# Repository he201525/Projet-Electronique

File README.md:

# Welcome in our Group Project for a course of Electricity!

***

We are a group of 4 students from EPHEC louvain la neuve. 
***

* Aymeric Ponjee
* Zita Almasy 
* Thibaut Hermant  
* Gauthier Bohyn

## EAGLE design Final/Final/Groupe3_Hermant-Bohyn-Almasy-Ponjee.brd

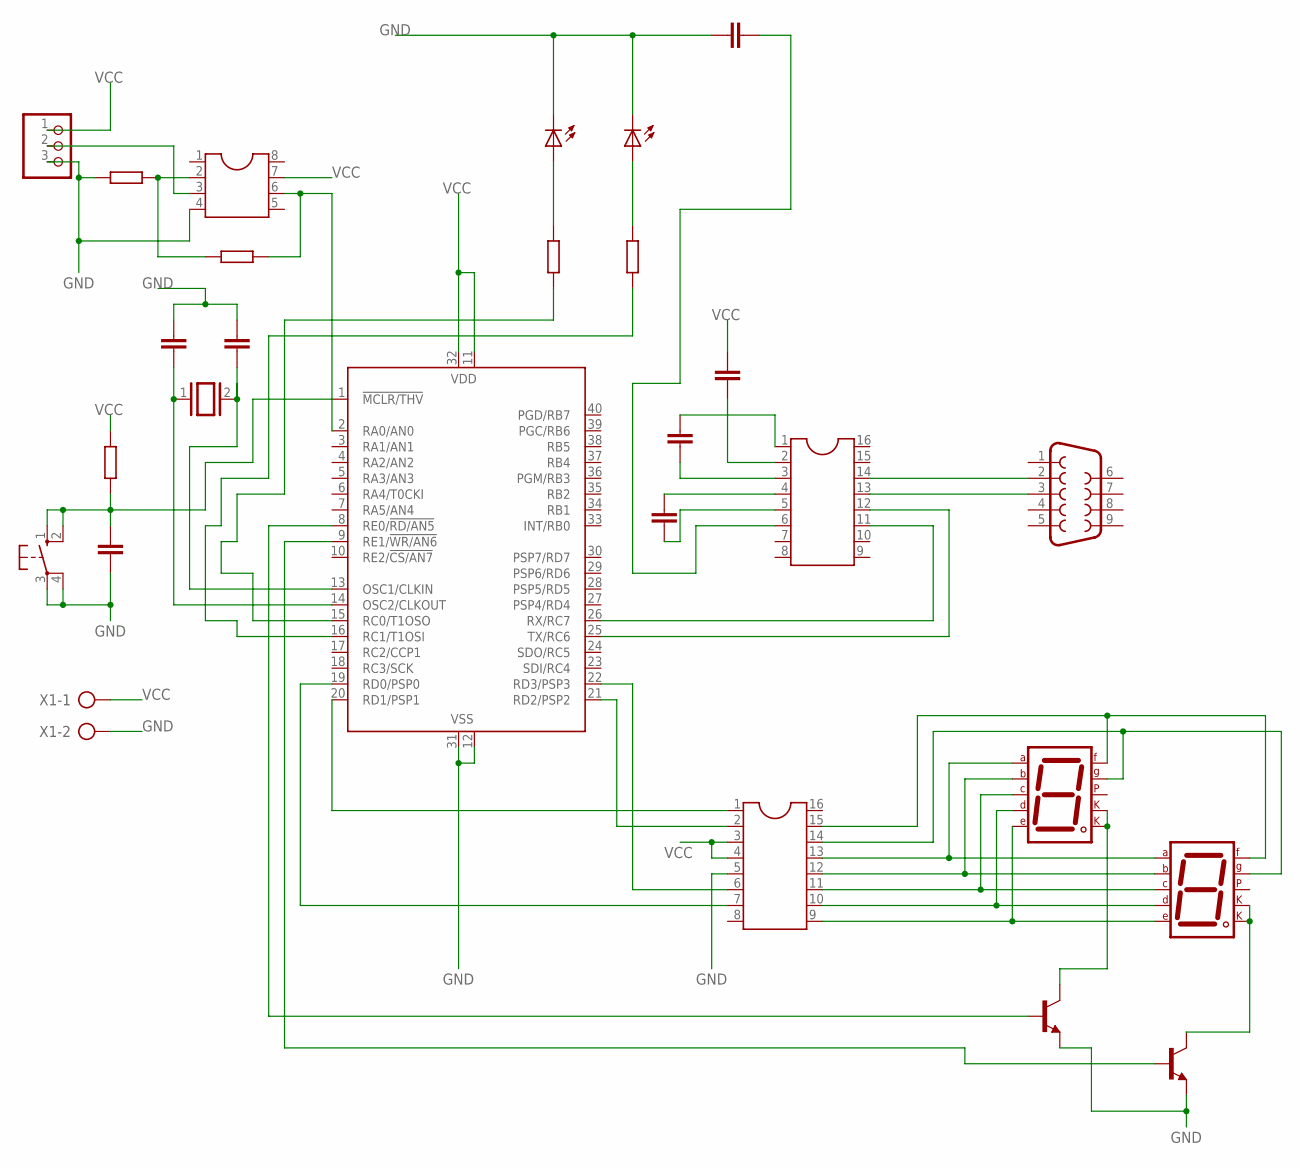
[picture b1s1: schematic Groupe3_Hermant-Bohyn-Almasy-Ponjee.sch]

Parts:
4511: DIL16
AMPLIOP: DIL8; DIL08
C1, C2: 15pF; C025-050X050
C3: 1uF; C025-050X050
C4, C5, C7, C61: 10uF; C025-050X050
D1, D2: 7SEG-CK; 7SEG-13
LED1, LED2: LED_ELD260; LED_LD260
LM35: PINHD-1X3; 1X03
MAX232: DIL16
P1/COMPIM: F09V
Q1, Q2: 2N2222; TO18
R1: 10k; 0204/7
R2: 4k; 0204/7
R3: 1k; 0204/7
R4, R5: 280; 0204/7
S1: 10-XX; B3F-10XX
U1: PIC16F877P; DIL40
X1: AK300/2
X11: XTAL/S; QS

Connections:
COMPIM: 4511.12, D1.6 (B), D2.6 (B)
GND: 4511.5, AMPLIOP.4, C1.1, C2.1, C3.1, C61.2, LED1.K (C), LED2.K (C), LM35.3, Q1.1 (E), Q2.1 (E), R2.1, S1.3, S1.4 (P1), U1.12 (VSS), U1.31 (VSS), X1.2
unnamed: C2.2, U1.14 (OSC2/CLKOUT), X11.1
unnamed: MAX232.14, P1/COMPIM.2
unnamed: LED2.A, R5.2
unnamed: C1.2, U1.13 (OSC1/CLKIN), X11.2
unnamed: 4511.1, U1.20 (RD1/PSP1)
unnamed: LED1.A, R4.2
unnamed: MAX232.13, P1/COMPIM.3
unnamed: C61.1, MAX232.6
unnamed: R4.1, U1.15 (RC0/T1OSO)
unnamed: R5.1, U1.16 (RC1/T1OSI)
unnamed: C7.1, MAX232.2
unnamed: C4.1, MAX232.3
unnamed: C4.2, MAX232.1
unnamed: C5.2, MAX232.4
unnamed: C5.1, MAX232.5
unnamed: C3.2, R1.1, S1.1 (S), S1.2 (S1), U1.1 (!MCLR/THV)
unnamed: 4511.7, U1.19 (RD0/PSP0)
unnamed: D1.3 (CK1), D1.8 (CK2), Q1.3 (C)
unnamed: 4511.2, U1.21 (RD2/PSP2)
unnamed: 4511.6, U1.22 (RD3/PSP3)
unnamed: AMPLIOP.3, LM35.2
unnamed: MAX232.12, U1.25 (TX/RC6)
unnamed: MAX232.11, U1.26 (RX/RC7)
unnamed: Q1.2 (B), U1.8 (RE0/!RD/AN5)
unnamed: AMPLIOP.2, R2.2, R3.1
unnamed: AMPLIOP.6, R3.2, U1.2 (RA0/AN0)
unnamed: 4511.13, D1.7 (A), D2.7 (A)
unnamed: 4511.10, D1.2 (D), D2.2 (D)
unnamed: 4511.11, D1.4 (C), D2.4 (C)
unnamed: 4511.9, D1.1 (E), D2.1 (E)
unnamed: 4511.14, D1.10 (G), D2.10 (G)
unnamed: D2.3 (CK1), D2.8 (CK2), Q2.3 (C)
unnamed: Q2.2 (B), U1.9 (RE1/!WR/AN6)
unnamed: 4511.15, D1.9 (F), D2.9 (F)
VCC: 4511.3, 4511.4, AMPLIOP.7, C7.2, LM35.1, R1.2, U1.11 (VDD), U1.32 (VDD), X1.1

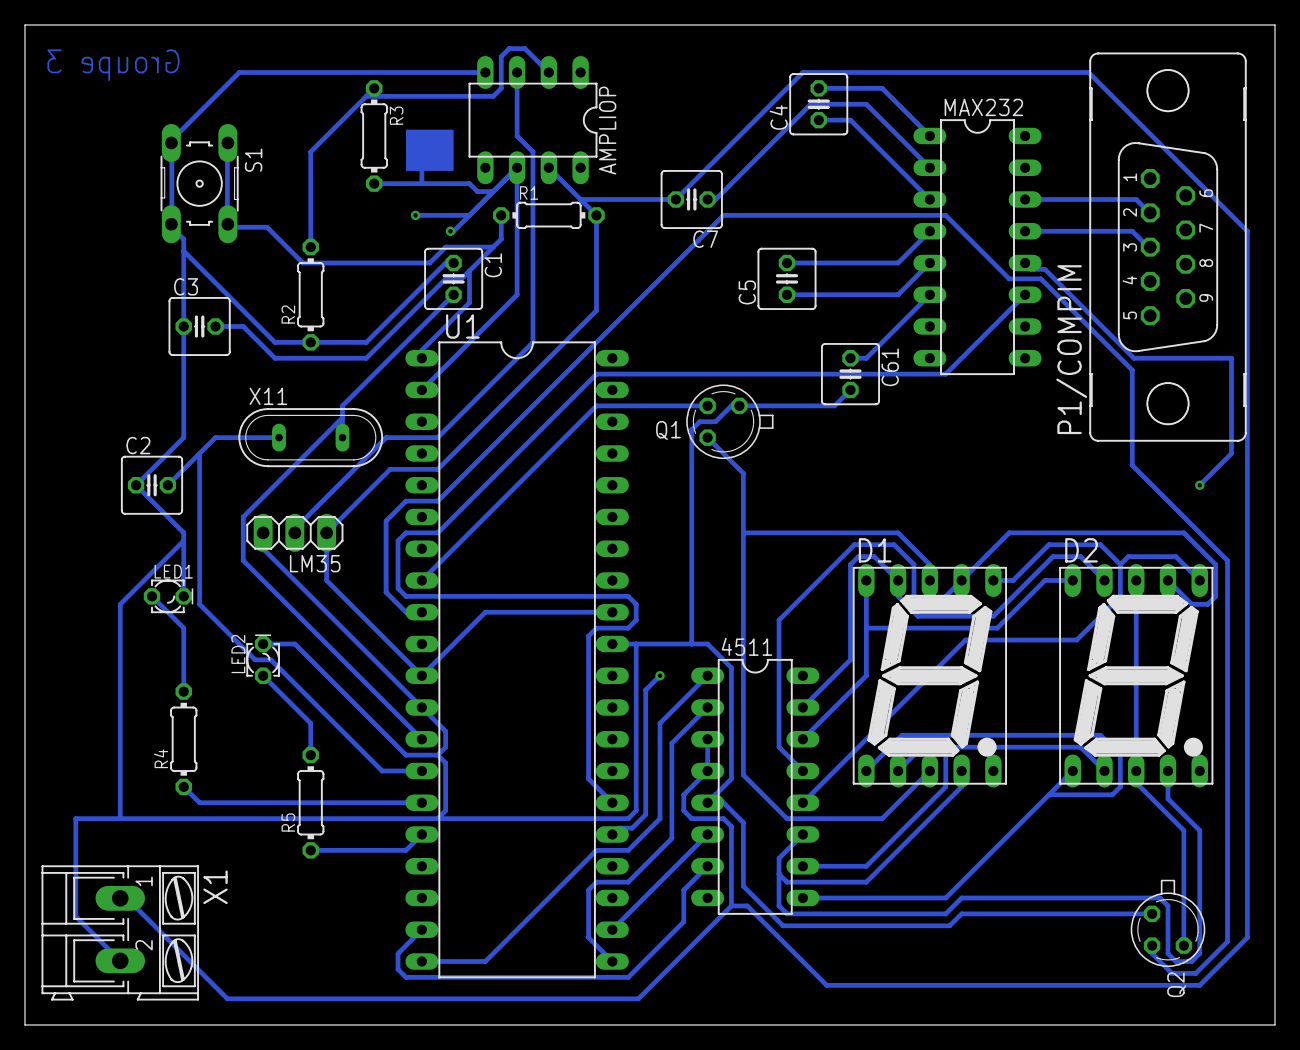
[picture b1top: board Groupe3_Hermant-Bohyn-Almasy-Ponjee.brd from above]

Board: 2 copper layers, 100.0 x 80.0 mm, 27 parts (0 on the bottom side), 37 nets.

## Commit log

2019-02-18 Create IMG&Files
2019-03-06 Ajout RP aux Leds
2019-03-10 Eagle-Elec.sch
    Première version
2019-03-11 Last update 97,3%
2019-03-11 Last update 97,3% (opt 4)
2019-03-11 Rename ElecBoardFinal.brd to Final/Groupe3_Hermant-Bohyn-Almasy-Ponjee.brd
2019-05-08 Create hello
2019-05-09 Rename main.STA to Code C/main.STA
2019-05-09 Rename main.c to Code C/main.c
2019-05-09 Rename main.ccspjt to Code C/main.ccspjt
2019-05-09 Rename main.err to Code C/main.err
2019-05-09 Rename main.esym to Code C/main.esym
2019-05-09 Rename main.h to Code C/main.h
2019-05-09 Rename main.hex to Code C/main.hex
2019-05-09 Rename main.lst to Code C/main.lst
2019-05-09 Rename main.sym to Code C/main.sym
2019-05-09 Rename main.tre to Code C/main.tre
2019-05-09 Create Rapport
2019-05-09 Create Intermédiaire
2019-05-09 Rename Rapport to Final
2019-05-19 Description de la Carte
